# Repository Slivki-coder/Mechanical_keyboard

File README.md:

# Keyboard

This is a Mechanical keyboard which I designed for highway, an event by hackclub. It includes a standard 80% layout as well as 5 macro keys on the left.

## CAD
I modeled all parts in Fusion 360. The case consists of 3 parts: The casing itself, a top plate for the switches and stabilizers and a stand to add a bit of incline to the keyboard. The stand and case each require 9 5x2mm magnets, which are used to attach the stand to the main body. It is also possible to add silicone feet to the stand to prevent it from sliding across the table. The top plate is fixed to the body with 7 M2.5x10 screws.

## PCB
The PCB & schematic was designed in KiCAD. The schematic is a bit confusing because some keys from col13 are shfted up one row.

## Firmware
The Firmware was created in python using the kmk library. It requires Circuitpython to be installed on the mcu to run. The Macro functions are currently empty, these can be set to any macro you want. KMK also does not have a Menu key so this one is currently set to KC.NO, but it can be repurposed as a layer switch for example.

## BOM

| Item           | Amount         | Total Price    | Required |
|----------------|----------------|----------------|----------|
| Neodymium Magnet 5x2mm  | 18  | 8€  | Yes |
| Rubber Pad 10mm | 2  | 4€  | Yes |
| M2.5x10 screw  | 7  | 11€  | Yes |
| Cherry MX switches | 92 | 75€ | Yes |
| Keycaps | 92 | 30€ | Yes |
| PCB | 1 | / | Yes |
| Raspberry Pi Pico | 1 | 10€ | Yes |
| 3d Printing Filament (any) | 1 spool | ~20€ | No |
| **Total** | | 158€ |

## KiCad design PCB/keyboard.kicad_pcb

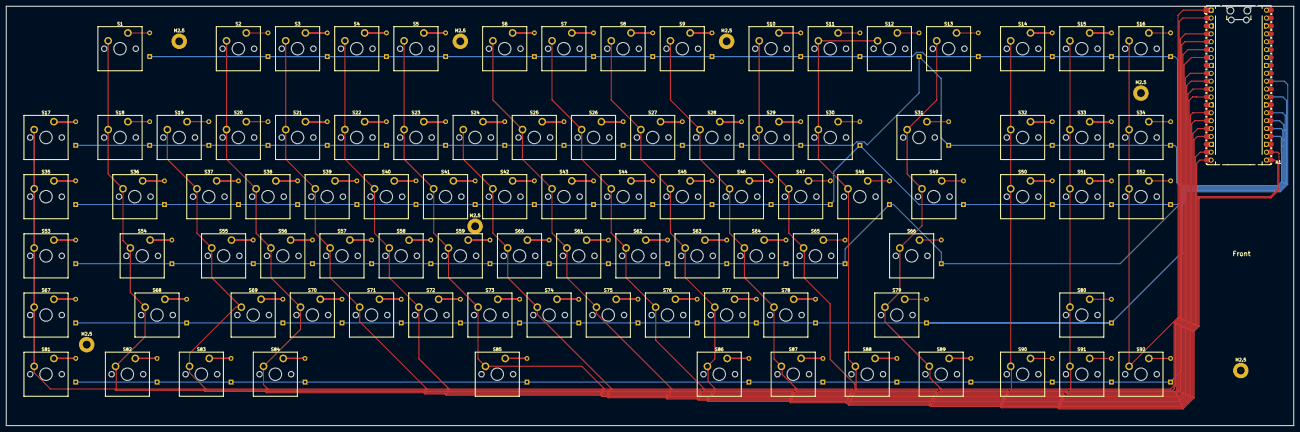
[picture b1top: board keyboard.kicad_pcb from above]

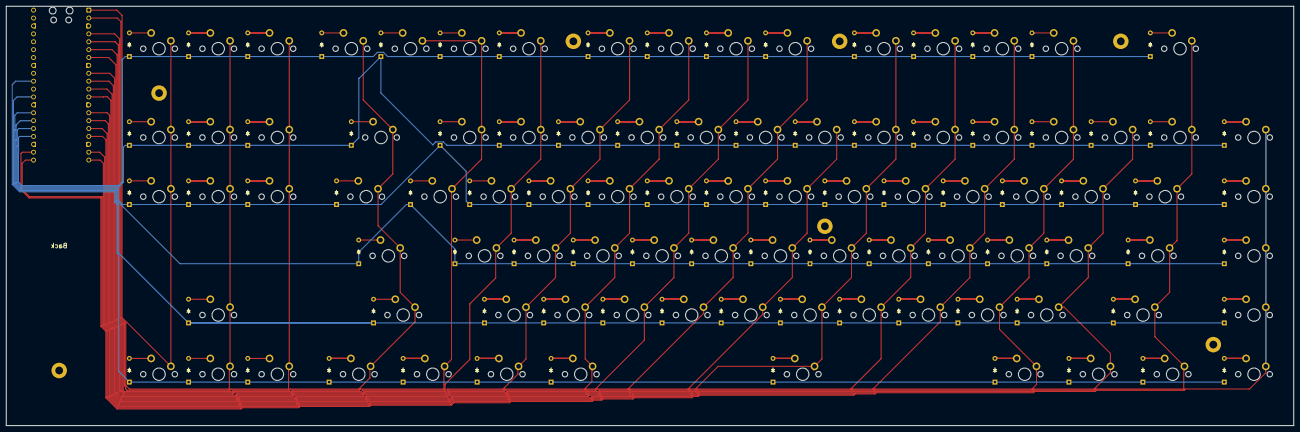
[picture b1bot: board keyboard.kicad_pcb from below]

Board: 2 copper layers, 414.4 x 135.0 mm, 192 parts (92 on the bottom side), 117 nets.

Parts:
A1: RaspberryPi_Pico; RaspberryPi_Pico_Common_Unspecified
D1, D2, D3, D4, D5, D6, D7, D8, D9, D10, D11, D12, D13, D14, D15, D16, D17, D18, D19, D20, D21, D22, D23, D24, D25, D26, D27, D28, D29, D30, D31, D32, D33, D34, D35, D36, D37, D38, D39, D40, D41, D42, D43, D44, D45, D46, D47, D48, D49, D50, D51, D52, D53, D54, D55, D56, D57, D58, D59, D60, D61, D62, D63, D64, D65, D66, D67, D68, D69, D70, D71, D72, D73, D74, D75, D76, D77, D78, D79, D80, D81, D82, D83, D84, D85, D86, D87, D88, D89, D90, D91, D92: Diode; Diode_DO-35
M2.5, M2.5#2, M2.5#3, M2.5#4, M2.5#5, M2.5#6, M2.5#7: MountingHole_2.5mm_Pad
S1, S2, S3, S4, S5, S6, S7, S8, S9, S10, S11, S12, S13, S14, S15, S16, S17, S18, S19, S20, S21, S22, S23, S24, S25, S26, S27, S28, S29, S30, S31, S32, S33, S34, S35, S36, S37, S38, S39, S40, S41, S42, S43, S44, S45, S46, S47, S48, S49, S50, S51, S52, S53, S54, S55, S56, S57, S58, S59, S60, S61, S62, S63, S64, S65, S66, S67, S68, S69, S70, S71, S72, S73, S74, S75, S76, S77, S78, S79, S80, S81, S82, S83, S84, S85, S86, S87, S88, S89, S90, S91, S92: Keyswitch; MX_PCB_1.00u

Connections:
unnamed: A1.3 (GND), A1.8 (GND), A1.13 (GND), A1.18 (GND), A1.23 (GND), A1.28 (GND), A1.38 (GND)
unnamed: D1.2 (A), S1.2
unnamed: D2.2 (A), S2.2
unnamed: D3.2 (A), S3.2
unnamed: D4.2 (A), S4.2
unnamed: D5.2 (A), S5.2
unnamed: D6.2 (A), S6.2
unnamed: D7.2 (A), S7.2
unnamed: D8.2 (A), S8.2
unnamed: D9.2 (A), S9.2
unnamed: D10.2 (A), S10.2
unnamed: D11.2 (A), S11.2
unnamed: D12.2 (A), S12.2
unnamed: D13.2 (A), S13.2
unnamed: D14.2 (A), S14.2
unnamed: D15.2 (A), S15.2
unnamed: D16.2 (A), S16.2
unnamed: D17.2 (A), S17.2
unnamed: D18.2 (A), S18.2
unnamed: D19.2 (A), S19.2
unnamed: D20.2 (A), S20.2
unnamed: D21.2 (A), S21.2
unnamed: D22.2 (A), S22.2
unnamed: D23.2 (A), S23.2
unnamed: D24.2 (A), S24.2
unnamed: D25.2 (A), S25.2
unnamed: D26.2 (A), S26.2
unnamed: D27.2 (A), S27.2
unnamed: D28.2 (A), S28.2
unnamed: D29.2 (A), S29.2
unnamed: D30.2 (A), S30.2
unnamed: D31.2 (A), S31.2
unnamed: D32.2 (A), S32.2
unnamed: D33.2 (A), S33.2
unnamed: D34.2 (A), S34.2
unnamed: D35.2 (A), S35.2
unnamed: D36.2 (A), S36.2
unnamed: D37.2 (A), S37.2
unnamed: D38.2 (A), S38.2
unnamed: D39.2 (A), S39.2
unnamed: D40.2 (A), S40.2
unnamed: D41.2 (A), S41.2
unnamed: D42.2 (A), S42.2
unnamed: D43.2 (A), S43.2
unnamed: D44.2 (A), S44.2
unnamed: D45.2 (A), S45.2
unnamed: D46.2 (A), S46.2
unnamed: D47.2 (A), S47.2
unnamed: D48.2 (A), S48.2
unnamed: D49.2 (A), S49.2
unnamed: D50.2 (A), S50.2
unnamed: D51.2 (A), S51.2
unnamed: D52.2 (A), S52.2
unnamed: D53.2 (A), S53.2
unnamed: D54.2 (A), S54.2
unnamed: D55.2 (A), S55.2
unnamed: D56.2 (A), S56.2
unnamed: D57.2 (A), S57.2
unnamed: D58.2 (A), S58.2
unnamed: D59.2 (A), S59.2
unnamed: D60.2 (A), S60.2
unnamed: D61.2 (A), S61.2
unnamed: D62.2 (A), S62.2
unnamed: D63.2 (A), S63.2
unnamed: D64.2 (A), S64.2
unnamed: D65.2 (A), S65.2
unnamed: D66.2 (A), S66.2
unnamed: D67.2 (A), S67.2
unnamed: D68.2 (A), S68.2
unnamed: D69.2 (A), S69.2
unnamed: D70.2 (A), S70.2
unnamed: D71.2 (A), S71.2
unnamed: D72.2 (A), S72.2
unnamed: D73.2 (A), S73.2
unnamed: D74.2 (A), S74.2
unnamed: D75.2 (A), S75.2
unnamed: D76.2 (A), S76.2
unnamed: D77.2 (A), S77.2
unnamed: D78.2 (A), S78.2
unnamed: D79.2 (A), S79.2
unnamed: D80.2 (A), S80.2
unnamed: D81.2 (A), S81.2
unnamed: D82.2 (A), S82.2
unnamed: D83.2 (A), S83.2
unnamed: D84.2 (A), S84.2
unnamed: D85.2 (A), S85.2
unnamed: D86.2 (A), S86.2
unnamed: D87.2 (A), S87.2
unnamed: D88.2 (A), S88.2
unnamed: D89.2 (A), S89.2
unnamed: D90.2 (A), S90.2
unnamed: D91.2 (A), S91.2
unnamed: D92.2 (A), S92.2
col0: A1.22 (GPIO17), S17.1, S35.1, S53.1, S67.1, S81.1
col1: A1.21 (GPIO16), S1.1, S18.1, S36.1, S54.1, S68.1, S82.1
col2: A1.20 (GPIO15), S19.1, S37.1, S55.1, S69.1, S83.1
col3: A1.19 (GPIO14), S2.1, S20.1, S38.1, S56.1, S70.1, S84.1
col4: A1.17 (GPIO13), S3.1, S21.1, S39.1, S57.1, S71.1
col5: A1.16 (GPIO12), S4.1, S22.1, S40.1, S58.1, S72.1
col6: A1.15 (GPIO11), S5.1, S23.1, S41.1, S59.1, S73.1, S85.1
col7: A1.14 (GPIO10), S24.1, S42.1, S60.1, S74.1
col8: A1.12 (GPIO9), S6.1, S25.1, S43.1, S61.1, S75.1
col9: A1.11 (GPIO8), S7.1, S26.1, S44.1, S62.1, S76.1
col10: A1.10 (GPIO7), S8.1, S27.1, S45.1, S63.1, S77.1, S86.1
col11: A1.9 (GPIO6), S9.1, S28.1, S46.1, S64.1, S78.1, S87.1
col12: A1.7 (GPIO5), S10.1, S29.1, S47.1, S65.1
col13: A1.6 (GPIO4), S11.1, S12.1, S30.1, S48.1, S88.1
col14: A1.5 (GPIO3), S13.1, S31.1, S49.1, S66.1, S79.1, S89.1
col15: A1.4 (GPIO2), S14.1, S32.1, S50.1, S90.1
col16: A1.2 (GPIO1), S15.1, S33.1, S51.1, S80.1, S91.1
col17: A1.1 (GPIO0), S16.1, S34.1, S52.1, S92.1
row0: A1.24 (GPIO18), D1.1 (K), D2.1 (K), D3.1 (K), D4.1 (K), D5.1 (K), D6.1 (K), D7.1 (K), D8.1 (K), D9.1 (K), D10.1 (K), D11.1 (K), D13.1 (K), D14.1 (K), D15.1 (K), D16.1 (K)
row1: A1.25 (GPIO19), D12.1 (K), D17.1 (K), D18.1 (K), D19.1 (K), D20.1 (K), D21.1 (K), D22.1 (K), D23.1 (K), D24.1 (K), D25.1 (K), D26.1 (K), D27.1 (K), D28.1 (K), D29.1 (K), D31.1 (K), D32.1 (K), D33.1 (K), D34.1 (K)
row2: A1.26 (GPIO20), D30.1 (K), D35.1 (K), D36.1 (K), D37.1 (K), D38.1 (K), D39.1 (K), D40.1 (K), D41.1 (K), D42.1 (K), D43.1 (K), D44.1 (K), D45.1 (K), D46.1 (K), D47.1 (K), D49.1 (K), D50.1 (K), D51.1 (K), D52.1 (K)
row3: A1.27 (GPIO21), D48.1 (K), D53.1 (K), D54.1 (K), D55.1 (K), D56.1 (K), D57.1 (K), D58.1 (K), D59.1 (K), D60.1 (K), D61.1 (K), D62.1 (K), D63.1 (K), D64.1 (K), D65.1 (K), D66.1 (K)
row4: A1.29 (GPIO22), D67.1 (K), D68.1 (K), D69.1 (K), D70.1 (K), D71.1 (K), D72.1 (K), D73.1 (K), D74.1 (K), D75.1 (K), D76.1 (K), D77.1 (K), D78.1 (K), D79.1 (K), D80.1 (K)
row5: A1.31 (GPIO26_ADC0), D81.1 (K), D82.1 (K), D83.1 (K), D84.1 (K), D85.1 (K), D86.1 (K), D87.1 (K), D88.1 (K), D89.1 (K), D90.1 (K), D91.1 (K), D92.1 (K)

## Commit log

2025-06-27 Add journal entry from yesterday
2025-07-01 added firmware
2025-07-02 added all files, updated README
2025-07-02 added BOM file
2025-07-18 Added fusion project file
2025-07-18 Please enter the commit message for your changes. Lines starting moved file into correct folder
2025-07-31 Updated files
